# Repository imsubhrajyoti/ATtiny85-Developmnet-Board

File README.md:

# ATtiny85-Developmnet-Board

ATTiny85 is an 8-bit AVR RISC microcontroller available in packages like PDIP, SOIC, QNC, MLF etc. It has 8KB of flash memory, 512B of SRAM and 512B of EEPROM. It has 8 pins, 6 I/O pins among which there are 3 Analog Pins and 2 PWM pins. This microcontroller also has MISO & MOSI pins and SDA & SCL pins. This microcontroller is compatible with Arduino IDE
For this board I have used the SOIC package. The features of this board are:
*	It is compatible with breadboard.
*	It has both 5V and 3.3V output pins
*	It can be powered using both USB and a PWR pin
*	It has an on board reset button for manual reset.

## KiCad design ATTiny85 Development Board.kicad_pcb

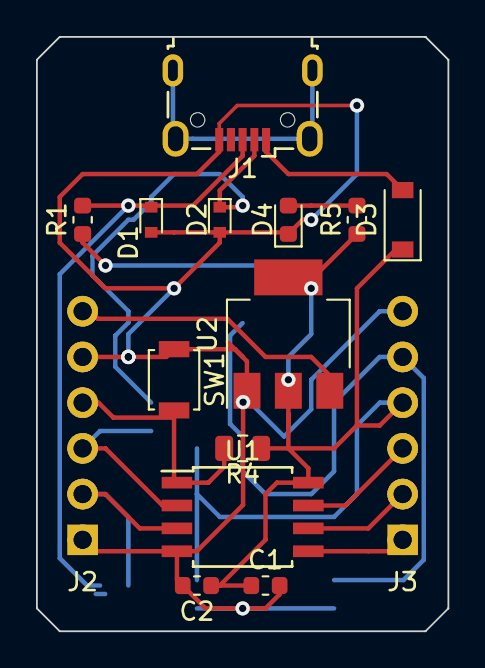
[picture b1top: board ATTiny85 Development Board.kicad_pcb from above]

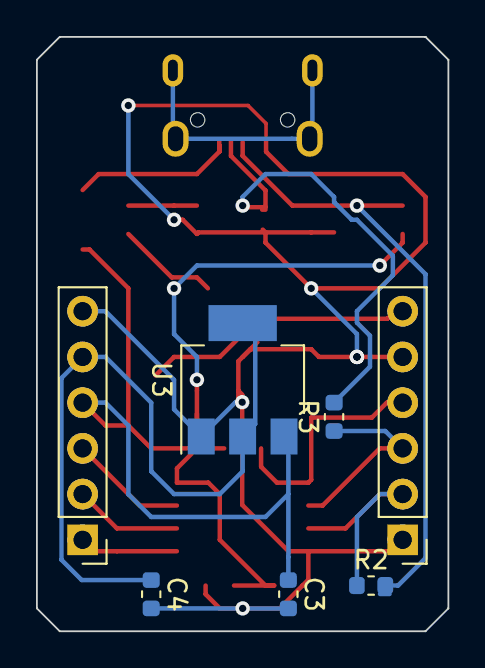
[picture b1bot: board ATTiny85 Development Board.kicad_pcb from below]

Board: 2 copper layers, 22.9 x 33.0 mm, 20 parts (7 on the bottom side), 14 nets.

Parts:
C1: 4.7MicroF; C_0603_1608Metric
C2: 0.1MicroF; C_0603_1608Metric
C3: 10MicroF; C_0603_1608Metric
C4: 22MicroF; C_0603_1608Metric
D1, D2: 3.6V; D_SOD-523
D3: MBR0520; D_SOD-123
D4: LED; LED_0603_1608Metric
J1: USB_B_Micro; USB_Micro-B_Wuerth_629105150521
J2: LConn; PinHeader_1x06_P2.54mm_Vertical
J3: RConn; PinHeader_1x06_P2.54mm_Vertical
R1: 1KOhm; R_0603_1608Metric
R2, R3: 68R; R_0603_1608Metric
R4: 10KOhm; R_0805_2012Metric_Pad1.15x1.40mm_HandSolder
R5: 220R; R_0603_1608Metric
SW1: SW_DIP_x01; SW_SPST_B3U-1000P
U1: ATtiny85-20SU; SOIJ-8_5.3x5.3mm_P1.27mm
U2: AMS1117-5.0; SOT-223-3_TabPin2
U3: AMS1117-3.3; SOT-223-3_TabPin2

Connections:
+3V3: C4.1, J3.5, U3.2
+5V: C1.1, C2.1, C3.1, D3.1, J3.4, R1.1, R4.1, R5.1, U1.8, U2.2, U3.3
GND: C1.2, C2.2, C3.2, C4.2, D1.2, D2.2, D4.1, J1.5, J2.1, J2.5, J3.6, SW1.1, U1.4, U2.1, U3.1
unnamed: D1.1, J1.3, R1.2, R2.2
unnamed: D2.1, J1.2, R3.2
unnamed: D4.2, R5.2
PB0: J3.1, U1.5
PB1: J3.2, U1.6
PB2: J3.3, U1.7
PB3: J2.3, R3.1, U1.2
PB4: J2.2, R2.1, U1.3
Reset: J2.4, R4.2, SW1.2, U1.1
VBUS: D3.2, J1.1
VCC: J2.6, U2.3

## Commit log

2020-11-18 Added Schematic File
2020-11-18 Added kicad_pcb File
2020-11-18 Added Netlist File
2020-11-18 Added Gerber Files
2020-11-18 Added Drill Files
